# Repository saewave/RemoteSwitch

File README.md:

# RemoteSwitch

Проект RemoteSwitch создан для тех, кто самостоятельно занимается разработкой систем домайшеней автоматизации но сталкивается с рядом проблем, таких как:
- передача данных по радио каналу;
- разработка схемотехники для исполнительных устройств;
- разработка модуля для управления устройствами (хаб);
- организации беспроводной сети.

Проект домашней автоматизации на базе SaeWave RemoteSwitch решает полностью или частично все вышеперечисленные проблемы. На данный момент характеристики системы такие:
- Частота радиоканала 433 МГц.
- Скорость передачи данных от 1200 кБит
- Дальность устойчивого приема на открытом пространстве - 300м (дальность зависит от помех, наличия препятствий и используемых антенн).
- Подтверждение приема - да (при соответствующих настройках)
- Повторение отправки пакета - да (при соответствующих настройках)
- Подпись пакета - CRC
- Возможность обновления прошивки по воздуху

Проект является полностью открытыми, все исходные коды, схемы и списки деталей являются общедоступными для использования и повторения.

Проект распространяется под лицензией GPLv3 - это означает то, что если ваш проект будет полностью или частично построен на базе SaeWave RemoteSwitch он должен быть открытым.

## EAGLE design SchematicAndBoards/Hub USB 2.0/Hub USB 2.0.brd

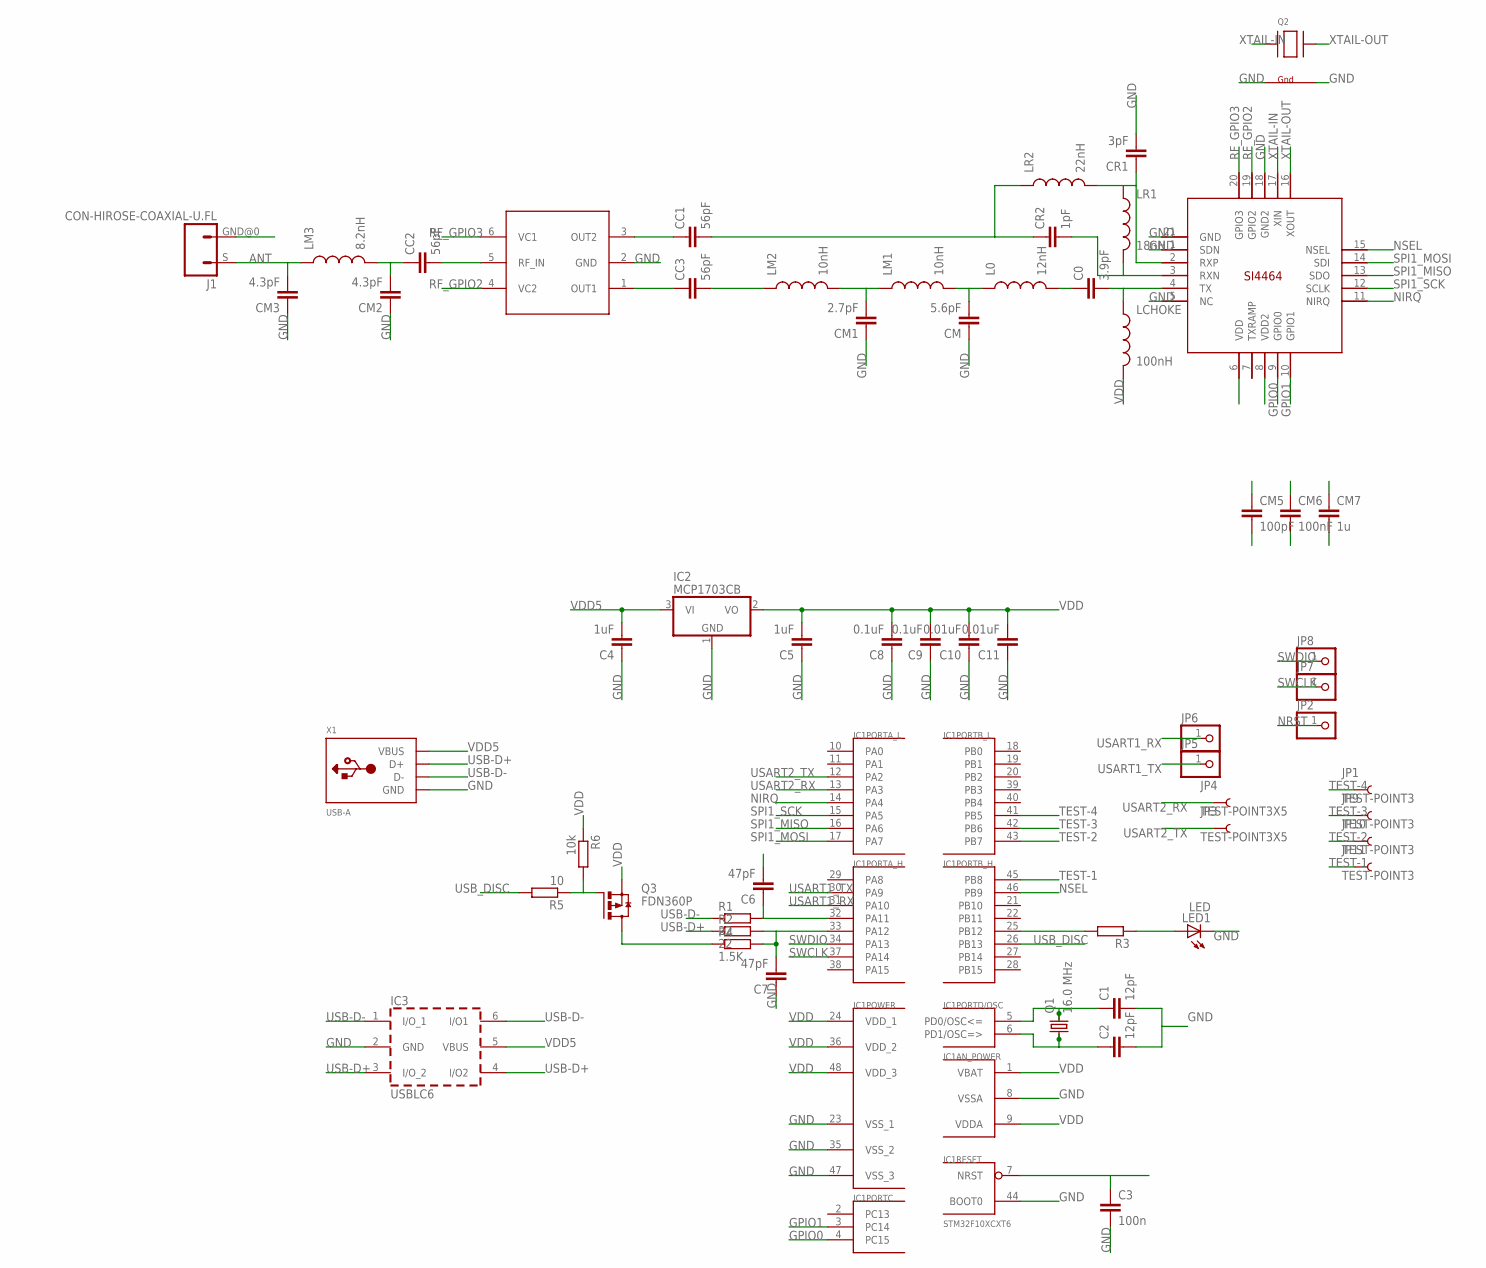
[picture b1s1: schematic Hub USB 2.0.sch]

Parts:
C0: 3.9pF; C0402
C1, C2: 12pF; C0603K
C3: 100n; C0805
C4, C5: 1uF; C0805
C6, C7: 47pF; C0805
C8, C9: 0.1uF; C0805
C10, C11: 0.01uF; C0805
CC1, CC2, CC3: 56pF; C0402
CM: 5.6pF; C0402
CM1: 2.7pF; C0402
CM2, CM3: 4.3pF; C0402
CM5: 100pF; C0402
CM6: 100nF; C0402
CM7: 1u; C0402
CR1: 3pF; C0402
CR2: 1pF; C0402
IC1: STM32F10XCXT6; TQFP48
IC2: MCP1703CB; SOT23
IC3: USBLC6; SOT-23-6L
J1: CON-HIROSE-COAXIAL-U.FL; CON-U.FL
JP1, JP9, JP10, JP11: TEST-POINT3; PAD.03X.03
JP2, JP7, JP8: PINHD-1X1; 1X01
JP3, JP4: TEST-POINT3X5; PAD.03X.05
JP5, JP6: PINHD-1X1CB; 1X01-CLEANBIG
L0: 12nH; C0402
LCHOKE: 100nH; C0402
LED1: LED; CHIPLED_0805
LM1, LM2: 10nH; C0402
LM3: 8.2nH; C0402
LR1: 18nH; C0402
LR2: 22nH; C0402
Q1: 16.0 MHz; CRYSTAL-SMD-3.2X2.5
Q2: XTAL-4-3225; NX3225
Q3: FDN360P; SUPER-SOT3
R1, R2: 22; R0805
R3: R-EU_R0805; R0805
R4: 1.5K; R0805
R5: 10; R0805
R6: 10k; R0805
U$1: SI4464; QFN20+GNDPAD
U$2: UPG2179TB; SUPER_MINIMOLD
X1: USB-A; MOLEX_480371000

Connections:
ANT: CM3.2, J1.S (1), LM3.1
GND: C1.2, C2.2, C3.2, C4.1, C5.1, C6.2, C7.1, C8.1, C9.1, C10.1, C11.1, CM.1, CM1.1, CM2.1, CM3.1, CM5.2, CM6.2, CM7.2, CR1.2, IC1.8 (VSSA), IC1.23 (VSS_1), IC1.35 (VSS_2), IC1.44 (BOOT0), IC1.47 (VSS_3), IC2.1 (GND), IC3.2 (GND), J1.GND@0 (2), LED1.C, Q2.2 (G2), Q2.4 (G1), U$1.1 (SDN), U$1.5 (NC), U$1.18 (GND2), U$1.21 (GND), U$2.2 (GND), X1.4 (GND)
GPIO0: IC1.4 (PC15), U$1.9 (GPIO0)
GPIO1: IC1.3 (PC14), U$1.10 (GPIO1)
unnamed: C1.1, IC1.5 (PD0/OSC<=), Q1.3 (2)
unnamed: C2.1, IC1.6 (PD1/OSC=>), Q1.1
unnamed: C0.2, LCHOKE.1, U$1.4 (TX)
unnamed: LED1.A, R3.1
unnamed: C0.1, L0.2
unnamed: C7.2, IC1.33 (PA12), R2.2, R4.2
unnamed: CM.2, L0.1, LM1.2
unnamed: CM1.2, LM1.1, LM2.2
unnamed: CC2.1, CM2.2, LM3.2
unnamed: C6.1, IC1.32 (PA11), R1.2
unnamed: CC3.1, U$2.1 (OUT1)
unnamed: CR2.2, LR1.2, U$1.3 (RXN)
unnamed: CC1.1, U$2.3 (OUT2)
unnamed: CR1.1, LR1.1, LR2.2, U$1.2 (RXP)
unnamed: IC1.25 (PB12), R3.2
unnamed: CC2.2, U$2.5 (RF_IN)
unnamed: CC3.2, LM2.1
unnamed: CC1.2, CR2.1, LR2.1
unnamed: Q3.3 (D), R4.1
unnamed: Q3.1 (G), R5.1, R6.2
NIRQ: IC1.14 (PA4), U$1.11 (NIRQ)
NRST: C3.1, IC1.7 (NRST), JP2.1
NSEL: IC1.46 (PB9), U$1.15 (NSEL)
RF_GPIO2: U$1.19 (GPIO2), U$2.4 (VC2)
RF_GPIO3: U$1.20 (GPIO3), U$2.6 (VC1)
SPI1_MISO: IC1.16 (PA6), U$1.13 (SDO)
SPI1_MOSI: IC1.17 (PA7), U$1.14 (SDI)
SPI1_SCK: IC1.15 (PA5), U$1.12 (SCLK)
SWCLK: IC1.37 (PA14), JP7.1
SWDIO: IC1.34 (PA13), JP8.1
TEST-1: IC1.45 (PB8), JP11.P$1
TEST-2: IC1.43 (PB7), JP10.P$1
TEST-3: IC1.42 (PB6), JP9.P$1
TEST-4: IC1.41 (PB5), JP1.P$1
USART1_RX: IC1.31 (PA10), JP6.1
USART1_TX: IC1.30 (PA9), JP5.1
USART2_RX: IC1.13 (PA3), JP4.P$1
USART2_TX: IC1.12 (PA2), JP3.P$1
USB-D+: IC3.3 (I/O_2), IC3.4 (I/O2), R2.1, X1.3 (D+)
USB-D-: IC3.1 (I/O_1), IC3.6 (I/O1), R1.1, X1.2 (D-)
USB_DISC: IC1.26 (PB13), R5.2
VDD: C5.2, C8.2, C9.2, C10.2, C11.2, CM5.1, CM6.1, CM7.1, IC1.1 (VBAT), IC1.9 (VDDA), IC1.24 (VDD_1), IC1.36 (VDD_2), IC1.48 (VDD_3), IC2.2 (VO), LCHOKE.2, Q3.2 (S), R6.1, U$1.6 (VDD), U$1.8 (VDD2)
VDD5: C4.2, IC2.3 (VI), IC3.5 (VBUS), X1.1 (VBUS)
XTAIL-IN: Q2.1 (X1), U$1.17 (XIN)
XTAIL-OUT: Q2.3 (X2), U$1.16 (XOUT)

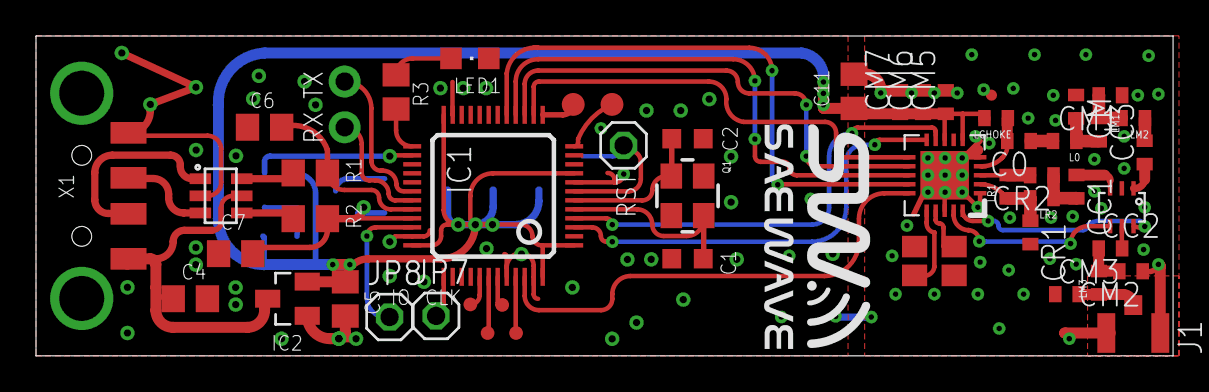
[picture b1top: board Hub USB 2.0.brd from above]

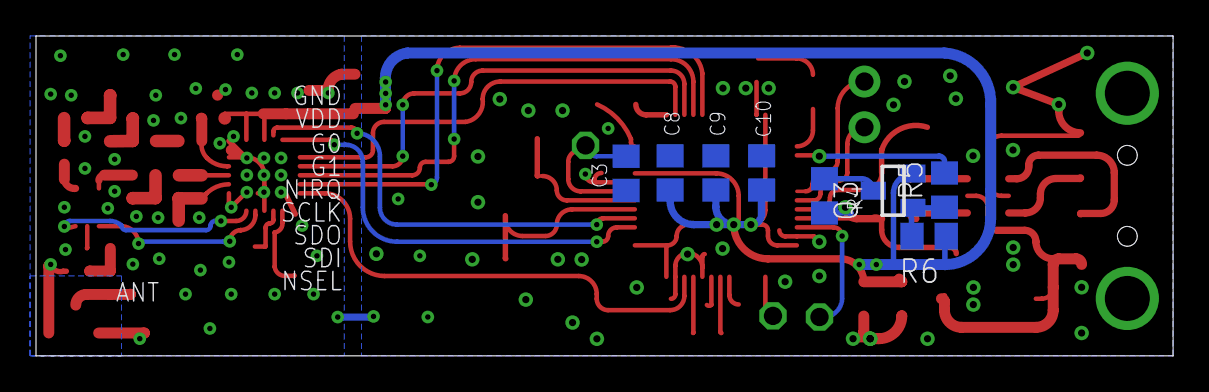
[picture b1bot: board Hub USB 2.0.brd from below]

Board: 2 copper layers, 63.2 x 17.8 mm, 59 parts (8 on the bottom side), 49 nets.

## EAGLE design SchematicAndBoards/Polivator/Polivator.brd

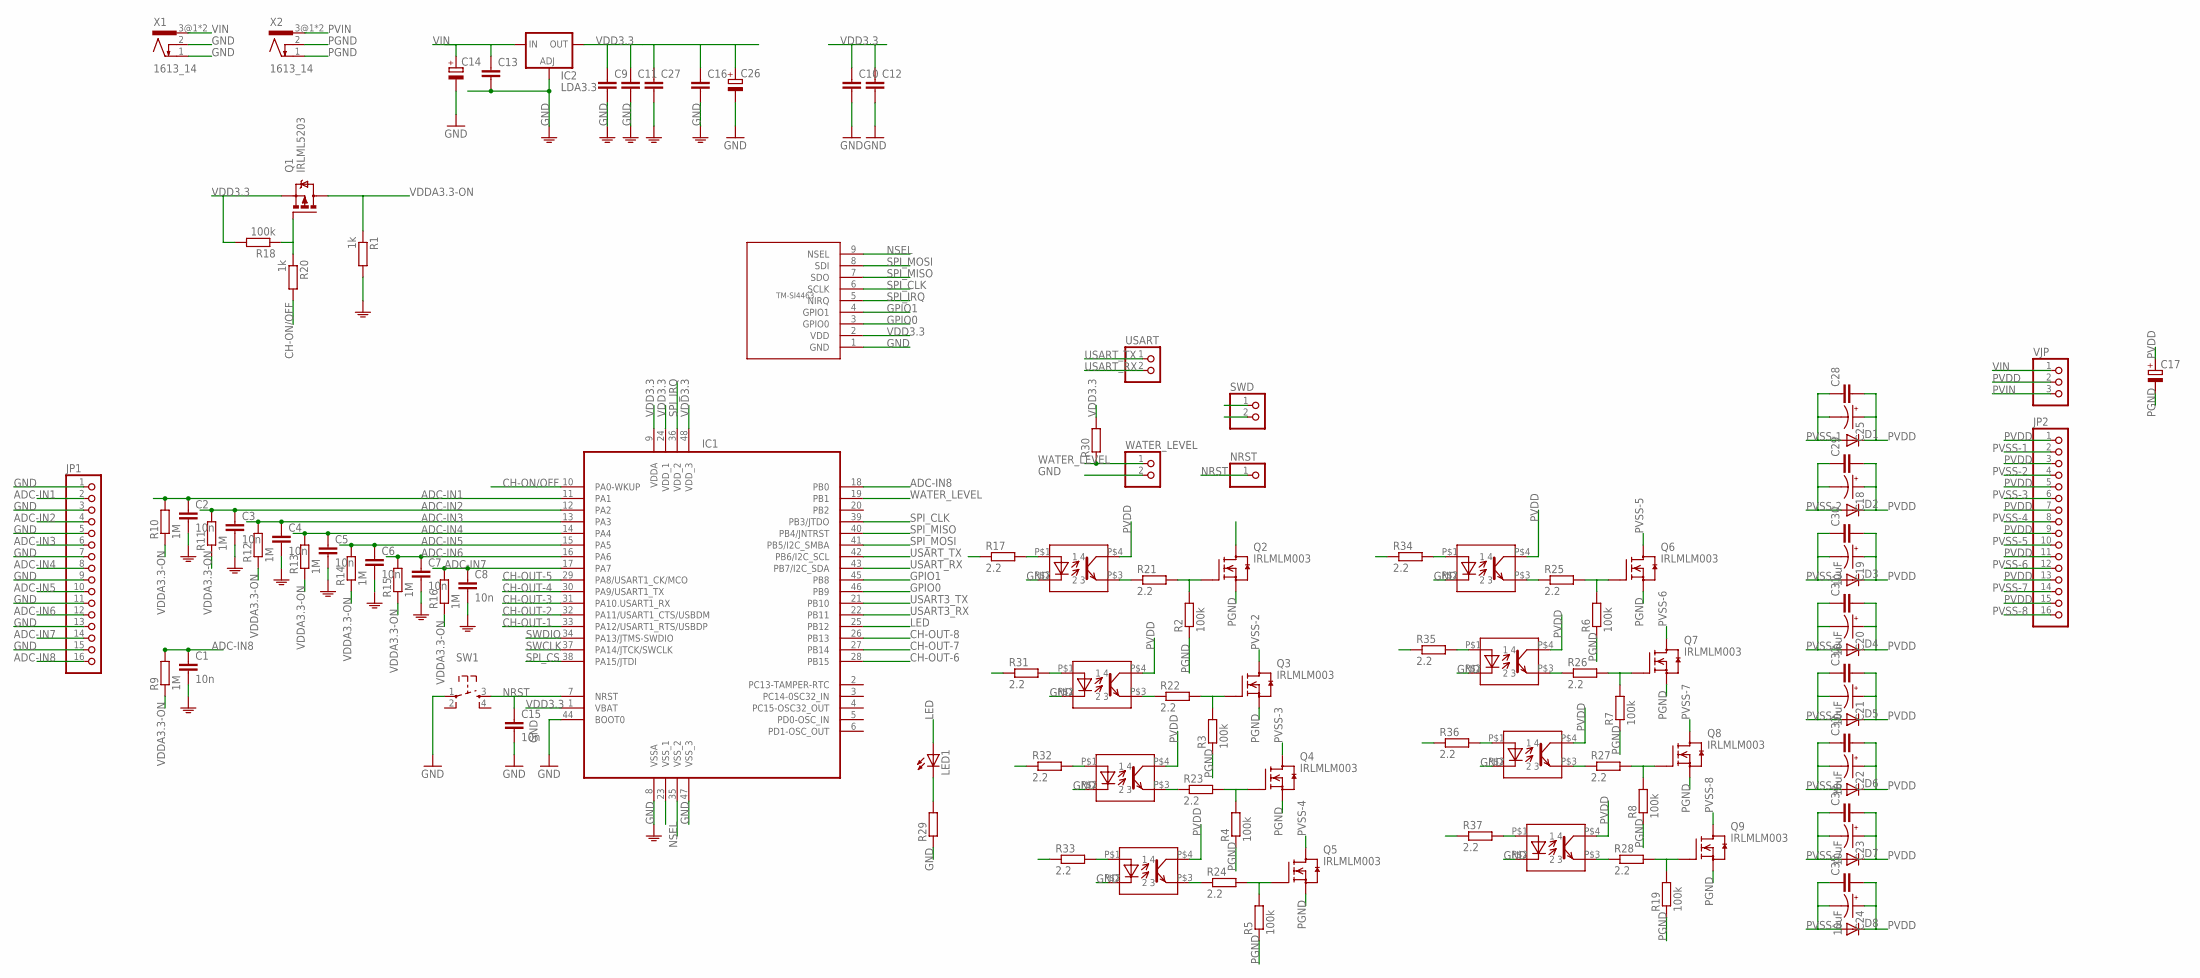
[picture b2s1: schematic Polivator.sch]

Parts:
C1, C2, C3, C4, C5, C6, C7, C8, C15: 10n; C0805
C9, C10: C-EUC3216; C3216
C11, C12, C16, C27, C28, C29, C30, C31, C32, C33, C34, C35: C-EUC0805; C0805
C13: C-EUC1808; C1808
C14, C26: CPOL-EUE2.5-5; E2,5-5
C17: CPOL-EUE2.5-6; E2,5-6
C18, C25: CAP_POL1206; EIA3216
C19, C20, C21, C22, C23, C24: 10uF; EIA3216
D1, D2, D3, D4, D5, D6, D7, D8: DIODE-SOD80C; SOD80C
IC1: IC_UC_STM32; LQFP48
IC2: LDA3.3; SOT223
JP1, JP2: PINHD-1X16; 1X16
LED1: LEDCHIPLED_0805; CHIPLED_0805
NRST: PINHD-1X1; 1X01
Q1: IRLML5203; MICRO3
Q2, Q3, Q4, Q5, Q6, Q7, Q8, Q9: IRLMLM003; SOT23
R1, R20: 1k; R0805
R2, R3, R4, R5, R6, R7, R8, R18, R19: 100k; R0805
R9, R10, R11, R12, R13, R14, R15, R16: 1M; R0805
R17, R21, R22, R23, R24, R25, R26, R27, R28, R31, R32, R33, R34, R35, R36, R37: 2.2; R0805
R29, R30: R-EU_R0805; R0805
SW1: SW_TACT_4P; SW_TACT_SMALL
SWD: PINHD-1X2; 1X02
U$8: TM-SI4463; TM-SI4463-SMD
U$10, U$11, U$13, U$16, U$18, U$20, U$23, U$24: PC817-SMD
USART: PINHD-1X2; 1X02
VJP: PINHD-1X3; 1X03
WATER_LEVEL: PINHD-1X2; 1X02
X1, X2: 1613_14

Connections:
ADC-IN1: C2.1, IC1.11 (PA1), JP1.2, R10.2
ADC-IN2: C3.1, IC1.12 (PA2), JP1.4, R11.2
ADC-IN3: C4.1, IC1.13 (PA3), JP1.6, R12.2
ADC-IN4: C5.1, IC1.14 (PA4), JP1.8, R13.2
ADC-IN5: C6.1, IC1.15 (PA5), JP1.10, R14.2
ADC-IN6: C7.1, IC1.16 (PA6), JP1.12, R15.2
ADC-IN7: C8.1, IC1.17 (PA7), JP1.14, R16.2
ADC-IN8: C1.1, IC1.18 (PB0), JP1.16, R9.2
CH-ON/OFF: IC1.10 (PA0-WKUP), R20.2
CH-OUT-1: IC1.33 (PA12/USART1_RTS/USBDP), R17.1
CH-OUT-2: IC1.32 (PA11/USART1_CTS/USBDM), R31.1
CH-OUT-3: IC1.31 (PA10.USART1_RX), R32.1
CH-OUT-4: IC1.30 (PA9/USART1_TX), R33.1
CH-OUT-5: IC1.29 (PA8/USART1_CK/MCO), R34.1
CH-OUT-6: IC1.28 (PB15), R35.1
CH-OUT-7: IC1.27 (PB14), R36.1
CH-OUT-8: IC1.26 (PB13), R37.1
GND: C1.2, C2.2, C3.2, C4.2, C5.2, C6.2, C7.2, C8.2, C9.2, C10.2, C11.2, C12.2, C13.2, C14.-, C15.2, C16.2, C26.-, C27.2, IC1.8 (VSSA), IC1.23 (VSS_1), IC1.44 (BOOT0), IC1.47 (VSS_3), IC2.1 (ADJ), JP1.1, JP1.3, JP1.5, JP1.7, JP1.9, JP1.11, JP1.13, JP1.15, R1.2, R29.1, SW1.1, U$8.1 (GND), U$10.P$2 (2), U$11.P$2 (2), U$13.P$2 (2), U$16.P$2 (2), U$18.P$2 (2), U$20.P$2 (2), U$23.P$2 (2), U$24.P$2 (2), WATER_LEVEL.2, X1.1, X1.2
GPIO0: IC1.46 (PB9), U$8.3 (GPIO0)
GPIO1: IC1.45 (PB8), U$8.4 (GPIO1)
LED: IC1.25 (PB12), LED1.A
unnamed: LED1.C, R29.2
unnamed: Q2.1 (G), R2.2, R21.2
unnamed: Q3.1 (G), R3.2, R22.2
unnamed: Q1.1 (G), R18.1, R20.1
unnamed: Q4.1 (G), R4.2, R23.2
unnamed: R21.1, U$10.P$3 (3)
unnamed: R22.1, U$11.P$3 (3)
unnamed: Q5.1 (G), R5.2, R24.2
unnamed: Q6.1 (G), R6.2, R25.2
unnamed: Q7.1 (G), R7.2, R26.2
unnamed: Q8.1 (G), R8.2, R27.2
unnamed: Q9.1 (G), R19.2, R28.2
unnamed: R23.1, U$13.P$3 (3)
unnamed: R24.1, U$16.P$3 (3)
unnamed: R25.1, U$18.P$3 (3)
unnamed: R26.1, U$20.P$3 (3)
unnamed: R27.1, U$23.P$3 (3)
unnamed: R28.1, U$24.P$3 (3)
unnamed: R17.2, U$10.P$1 (1)
unnamed: R31.2, U$11.P$1 (1)
unnamed: R32.2, U$13.P$1 (1)
unnamed: R33.2, U$16.P$1 (1)
unnamed: R37.2, U$24.P$1 (1)
unnamed: R36.2, U$23.P$1 (1)
unnamed: R35.2, U$20.P$1 (1)
unnamed: R34.2, U$18.P$1 (1)
NRST: C15.1, IC1.7 (NRST), NRST.1, SW1.3
NSEL: IC1.35 (VSS_2), U$8.9 (NSEL)
PGND: C17.-, Q2.2 (S), Q3.2 (S), Q4.2 (S), Q5.2 (S), Q6.2 (S), Q7.2 (S), Q8.2 (S), Q9.2 (S), R2.1, R3.1, R4.1, R5.1, R6.1, R7.1, R8.1, R19.1, X2.1, X2.2
PVDD: C17.+, C18.A (+), C19.A (+), C20.A (+), C21.A (+), C22.A (+), C23.A (+), C24.A (+), C25.A (+), C28.2, C29.2, C30.2, C31.2, C32.2, C33.2, C34.2, C35.2, D1.C, D2.C, D3.C, D4.C, D5.C, D6.C, D7.C, D8.C, JP2.1, JP2.3, JP2.5, JP2.7, JP2.9, JP2.11, JP2.13, JP2.15, U$10.P$4 (4), U$11.P$4 (4), U$13.P$4 (4), U$16.P$4 (4), U$18.P$4 (4), U$20.P$4 (4), U$23.P$4 (4), U$24.P$4 (4), VJP.2
PVIN: VJP.3, X2.3@1 (3), X2.3@2 (3)
PVSS-1: C25.C (-), C28.1, D1.A, JP2.2, Q2.3 (D)
PVSS-2: C18.C (-), C29.1, D2.A, JP2.4, Q3.3 (D)
PVSS-3: C19.C (-), C30.1, D3.A, JP2.6, Q4.3 (D)
PVSS-4: C20.C (-), C31.1, D4.A, JP2.8, Q5.3 (D)
PVSS-5: C21.C (-), C32.1, D5.A, JP2.10, Q6.3 (D)
PVSS-6: C22.C (-), C33.1, D6.A, JP2.12, Q7.3 (D)
PVSS-7: C23.C (-), C34.1, D7.A, JP2.14, Q8.3 (D)
PVSS-8: C24.C (-), C35.1, D8.A, JP2.16, Q9.3 (D)
SPI_CLK: IC1.39 (PB3/JTDO), U$8.6 (SCLK)
SPI_CS: IC1.38 (PA15/JTDI)
SPI_IRQ: IC1.36 (VDD_2), U$8.5 (NIRQ)
SPI_MISO: IC1.40 (PB4/JNTRST), U$8.7 (SDO)
SPI_MOSI: IC1.41 (PB5/I2C_SMBA), U$8.8 (SDI)
SWCLK: IC1.37 (PA14/JTCK/SWCLK), SWD.2
SWDIO: IC1.34 (PA13/JTMS-SWDIO), SWD.1
USART3_RX: IC1.22 (PB11)
USART3_TX: IC1.21 (PB10)
USART_RX: IC1.43 (PB7/I2C_SDA), USART.2
USART_TX: IC1.42 (PB6/I2C_SCL), USART.1
VDD3.3: C9.1, C10.1, C11.1, C12.1, C16.1, C26.+, C27.1, IC1.1 (VBAT), IC1.9 (VDDA), IC1.24 (VDD_1), IC1.48 (VDD_3), IC2.4 (OUT), Q1.2 (S), R18.2, R30.2, U$8.2 (VDD)
VDDA3.3-ON: Q1.3 (D), R1.1, R9.1, R10.1, R11.1, R12.1, R13.1, R14.1, R15.1, R16.1
VIN: C13.1, C14.+, IC2.3 (IN), VJP.1, X1.3@1 (3), X1.3@2 (3)
WATER_LEVEL: IC1.19 (PB1), R30.1, WATER_LEVEL.1

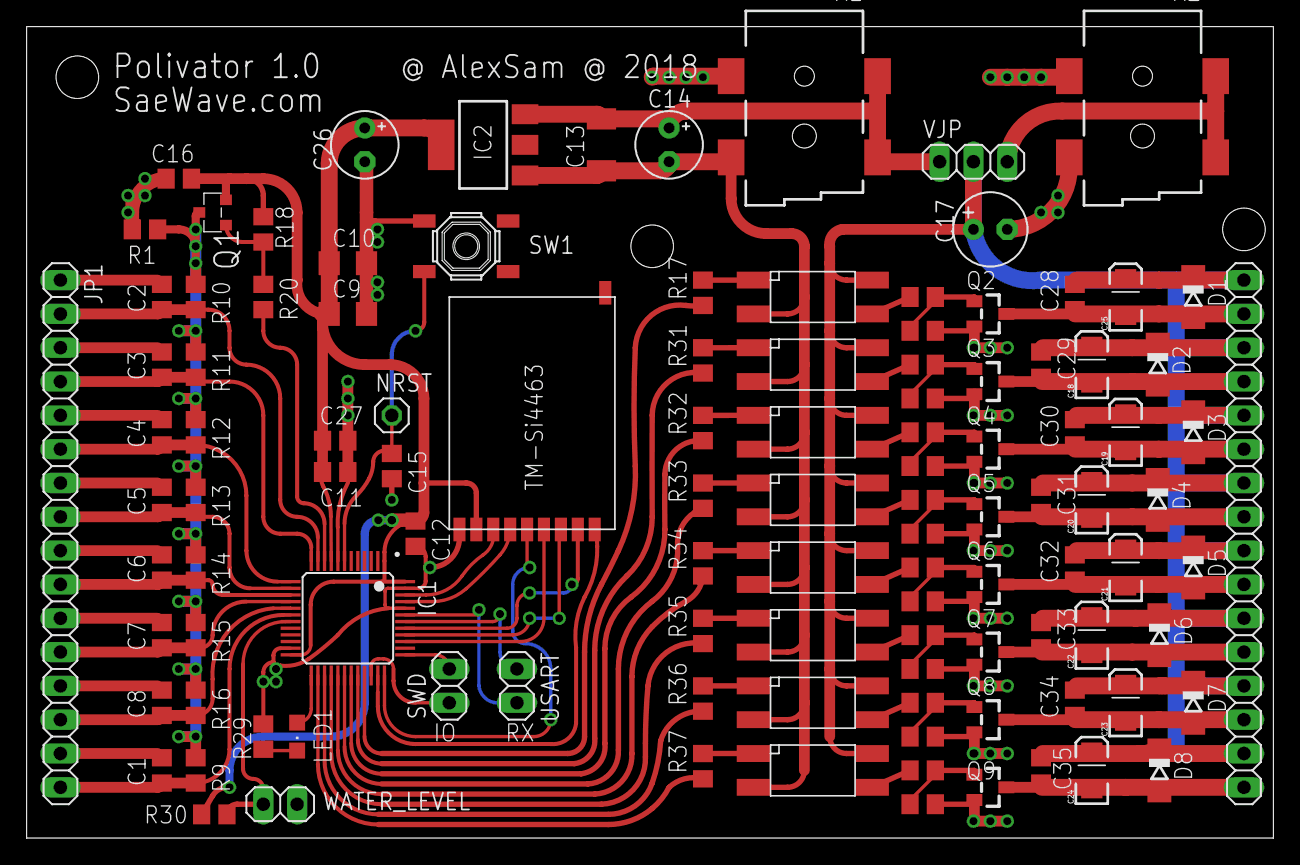
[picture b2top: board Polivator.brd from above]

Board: 2 copper layers, 93.7 x 61.0 mm, 111 parts (0 on the bottom side), 72 nets.

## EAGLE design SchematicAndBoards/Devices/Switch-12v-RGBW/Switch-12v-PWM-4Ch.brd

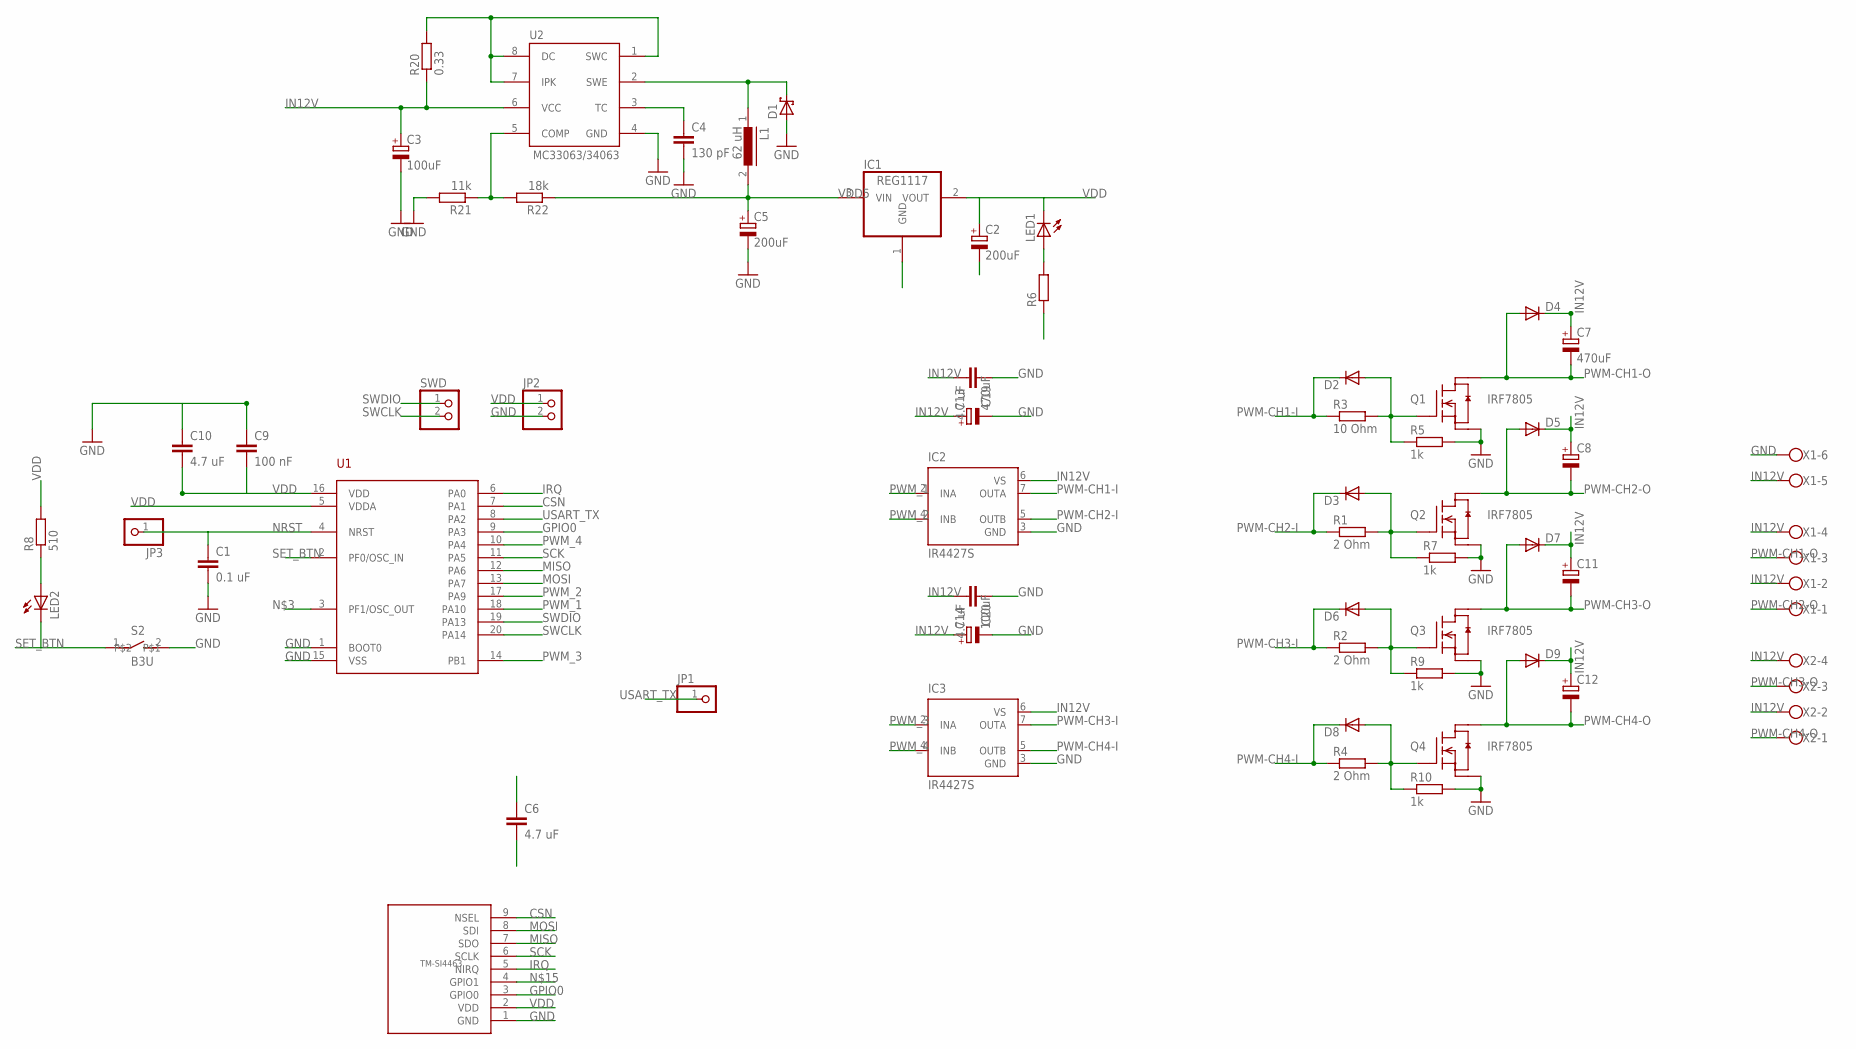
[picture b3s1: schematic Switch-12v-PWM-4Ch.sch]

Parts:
C1: 0.1 uF; C0805
C2, C5: 200uF; SMC_C
C3: 100uF; SMC_C
C4: 130 pF; C0805
C6, C10, C19, C20: 4.7 uF; C0805
C7: 470uF; E5-8,5
C8, C11, C12: CPOL-EUE5-8.5; E5-8,5
C9: 100 nF; C0805
C13: 470uF; 085CS_1AR
C14: 100uF; 085CS_1AR
D1: SCHOTTKY-DIODE; DIODE_SMB
D2, D3, D4, D5, D6, D7, D8, D9: DIODE-DO214BA; DO214BA
IC1: REG1117; SOT223
IC2, IC3: IR4427S; SO08
JP1, JP3: PINHD-1X1; 1X01
JP2: PINHD-1X2; 1X02
L1: 62 uH; DR73
LED1, LED2: LEDCHIPLED_0805; CHIPLED_0805
Q1, Q2, Q3, Q4: IRF7805; SO-8
R1, R2, R4: 2 Ohm; R0805
R3: 10 Ohm; R0805
R5, R7, R9, R10: 1k; R0805
R6: R-EU_R0805; R0805
R8: 510; R0805
R20: 0.33; R0805
R21: 11k; R0805
R22: 18k; R0805
S2: B3U; 1210
SWD: PINHD-1X2; 1X02
U1: STM32F030F4; TSSOP20
U2: MC33063/MC34063D; SO08
U$1: TM-SI4463; TM-SI4463-SMD
X1: W237-6
X2: W237-4

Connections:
CSN: U1.7 (PA1), U$1.9 (NSEL)
GND: C1.2, C2.-, C3.-, C4.2, C5.-, C6.2, C9.1, C10.1, C13.-, C14.-, C19.1, C20.1, D1.A (C), IC1.1 (GND), IC2.3 (GND), IC3.3 (GND), JP2.2, Q1.3 (S), Q2.3 (S), Q3.3 (S), Q4.3 (S), R5.2, R6.1, R7.2, R9.2, R10.2, R21.2, S2.2, U1.1 (BOOT0), U1.15 (VSS), U2.4 (GND), U$1.1 (GND), X1.6
GPIO0: U1.9 (PA3), U$1.3 (GPIO0)
IN12V: C3.+, C7.+, C8.+, C11.+, C12.+, C13.+, C14.+, C19.2, C20.2, D4.C, D5.C, D7.C, D9.C, IC2.6 (VS), IC3.6 (VS), R20.1, U2.6 (VCC), X1.2, X1.4, X1.5, X2.2, X2.4
IRQ: U1.6 (PA0), U$1.5 (NIRQ)
MISO: U1.12 (PA6), U$1.7 (SDO)
MOSI: U1.13 (PA7), U$1.8 (SDI)
unnamed: D2.A, Q1.4 (G), R3.2, R5.1
unnamed: D3.A, Q2.4 (G), R1.2, R7.1
unnamed: LED1.A, R6.2
unnamed: LED2.A, R8.1
unnamed: R21.1, R22.2, U2.5 (COMP)
unnamed: R20.2, U2.1 (SWC), U2.7 (IPK), U2.8 (DC)
unnamed: C4.1, U2.3 (TC)
unnamed: D1.C (A), L1.1, U2.2 (SWE)
unnamed: D6.A, Q3.4 (G), R2.2, R9.1
unnamed: D8.A, Q4.4 (G), R4.2, R10.1
NRST: C1.1, JP3.1, U1.4 (NRST)
PWM-CH1-I: D2.C, IC2.7 (OUTA), R3.1
PWM-CH1-O: C7.-, D4.A, Q1.8 (D), X1.3
PWM-CH2-I: D3.C, IC2.5 (OUTB), R1.1
PWM-CH2-O: C8.-, D5.A, Q2.8 (D), X1.1
PWM-CH3-I: D6.C, IC3.7 (OUTA), R2.1
PWM-CH3-O: C11.-, D7.A, Q3.8 (D), X2.3
PWM-CH4-I: D8.C, IC3.5 (OUTB), R4.1
PWM-CH4-O: C12.-, D9.A, Q4.8 (D), X2.1
PWM_1: IC2.2 (INA), U1.18 (PA10)
PWM_2: IC2.4 (INB), U1.17 (PA9)
PWM_3: IC3.2 (INA), U1.14 (PB1)
PWM_4: IC3.4 (INB), U1.10 (PA4)
SCK: U1.11 (PA5), U$1.6 (SCLK)
SET_BTN: LED2.C, S2.1, U1.2 (PF0/OSC_IN)
SWCLK: SWD.2, U1.20 (PA14)
SWDIO: SWD.1, U1.19 (PA13)
USART_TX: JP1.1, U1.8 (PA2)
VDD: C2.+, C6.1, C9.2, C10.2, IC1.2 (VOUT), JP2.1, LED1.C, R8.2, U1.5 (VDDA), U1.16 (VDD), U$1.2 (VDD)
VDD5: C5.+, IC1.3 (VIN), L1.2, R22.1

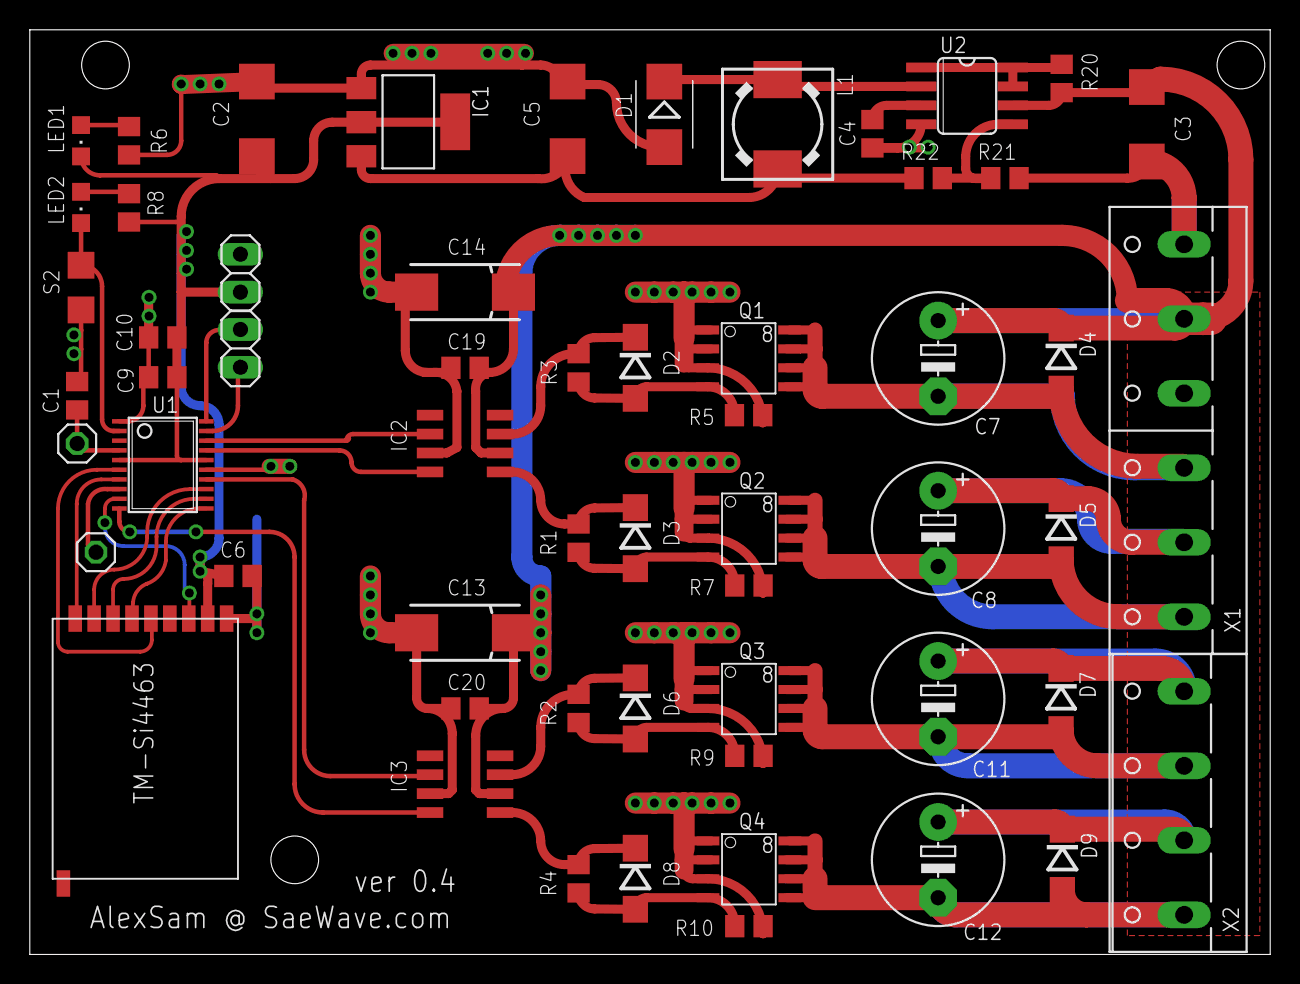
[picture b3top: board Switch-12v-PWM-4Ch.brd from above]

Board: 2 copper layers, 83.2 x 62.1 mm, 58 parts (0 on the bottom side), 37 nets.

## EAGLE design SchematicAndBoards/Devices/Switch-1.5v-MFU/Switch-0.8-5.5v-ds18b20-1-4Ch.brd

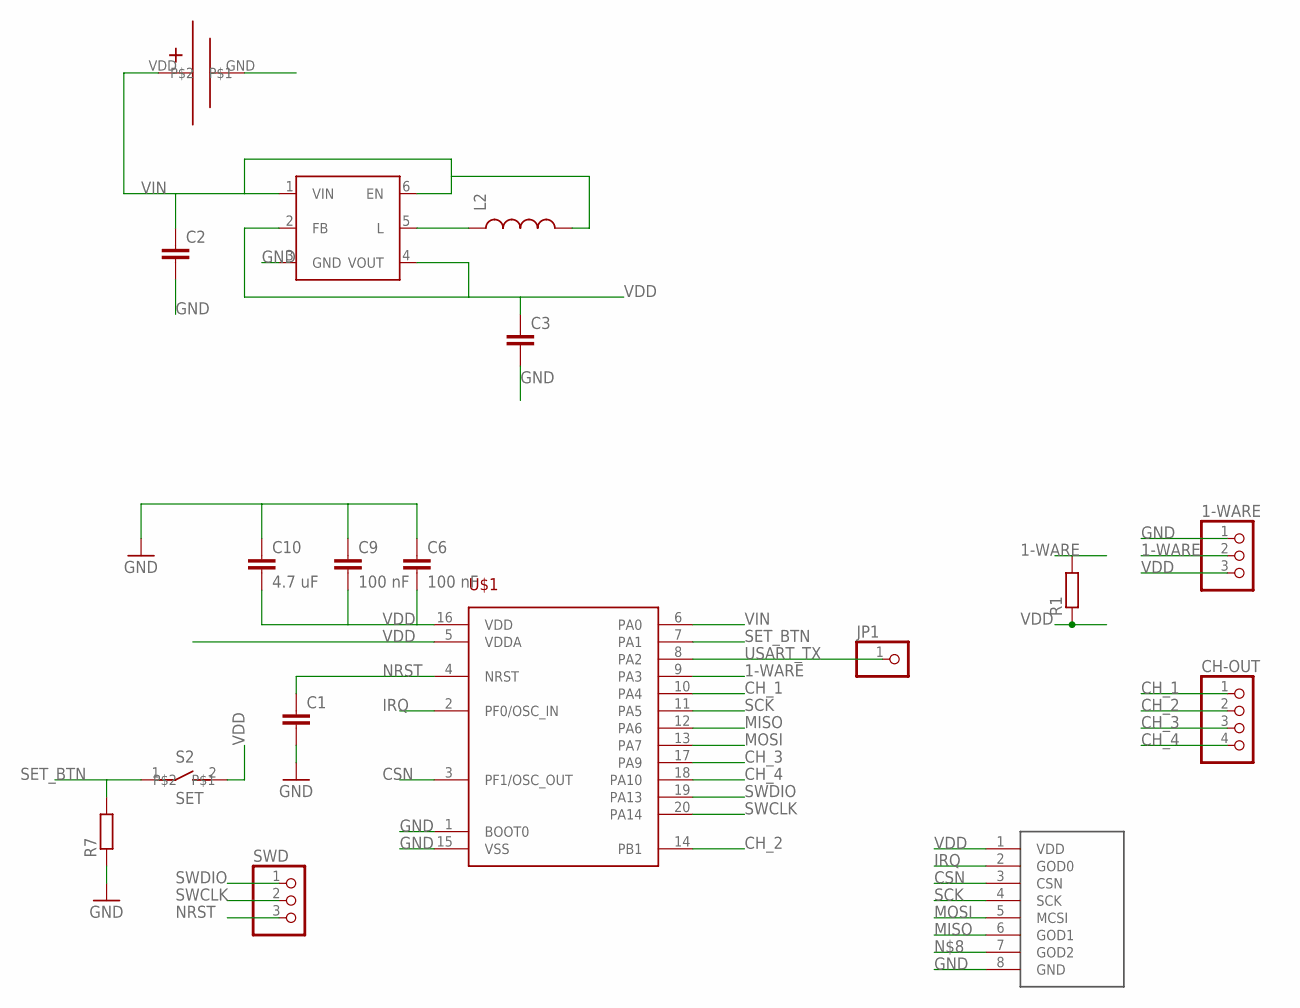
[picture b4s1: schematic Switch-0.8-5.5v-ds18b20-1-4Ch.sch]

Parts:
1-WARE: PINHD-1X3; 1X03
C1, C2, C3: C-EUC0805; C0805
C6, C9: 100 nF; C0805
C10: 4.7 uF; C0805
CH-OUT: PINHD-1X4_2.54; 1X04
JP1: PINHD-1X1CB; 1X01-CLEANBIG
L2: INDUCTOR1210; 1210
R1, R7: R-EU_R0805; R0805
S2: SET; 1210
SWD: PINHD-1X3CB; 1X03-CLEANBIG
U$1: STM32F030F4; TSSOP20
U$2: TPS61221; SC-70-6
U$3: AS07-M1101S
U$4: BAT-AA1-PCB-HOLDER

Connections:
1-WARE: 1-WARE.2, R1.2, U$1.9 (PA3)
CH_1: CH-OUT.1, U$1.10 (PA4)
CH_2: CH-OUT.2, U$1.14 (PB1)
CH_3: CH-OUT.3, U$1.17 (PA9)
CH_4: CH-OUT.4, U$1.18 (PA10)
CSN: U$1.3 (PF1/OSC_OUT), U$3.3 (CSN)
GND: 1-WARE.1, C1.2, C2.2, C3.2, C6.1, C9.1, C10.1, R7.1, U$1.1 (BOOT0), U$1.15 (VSS), U$2.3 (GND), U$3.8 (GND), U$4.GND
IRQ: U$1.2 (PF0/OSC_IN), U$3.2 (GOD0)
MISO: U$1.12 (PA6), U$3.6 (GOD1)
MOSI: U$1.13 (PA7), U$3.5 (MCSI)
unnamed: L2.1, U$2.5 (L)
NRST: C1.1, SWD.3, U$1.4 (NRST)
SCK: U$1.11 (PA5), U$3.4 (SCK)
SET_BTN: R7.2, S2.1, U$1.7 (PA1)
SWCLK: SWD.2, U$1.20 (PA14)
SWDIO: SWD.1, U$1.19 (PA13)
USART_TX: JP1.1, U$1.8 (PA2)
VDD: 1-WARE.3, C3.1, C6.2, C9.2, C10.2, R1.1, S2.2, U$1.5 (VDDA), U$1.16 (VDD), U$2.2 (FB), U$2.4 (VOUT), U$3.1 (VDD)
VIN: C2.1, L2.2, U$1.6 (PA0), U$2.1 (VIN), U$2.6 (EN), U$4.VDD

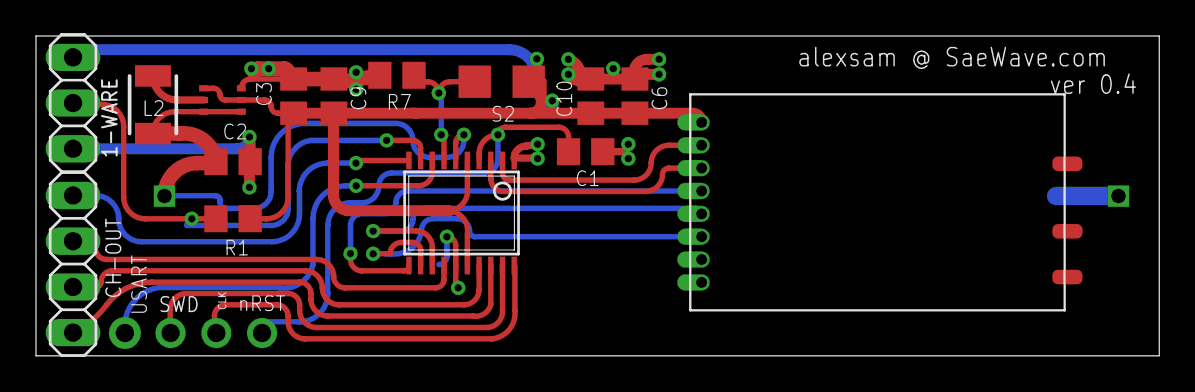
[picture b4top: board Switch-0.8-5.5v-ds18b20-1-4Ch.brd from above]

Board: 2 copper layers, 62.4 x 17.8 mm, 18 parts (1 on the bottom side), 19 nets.

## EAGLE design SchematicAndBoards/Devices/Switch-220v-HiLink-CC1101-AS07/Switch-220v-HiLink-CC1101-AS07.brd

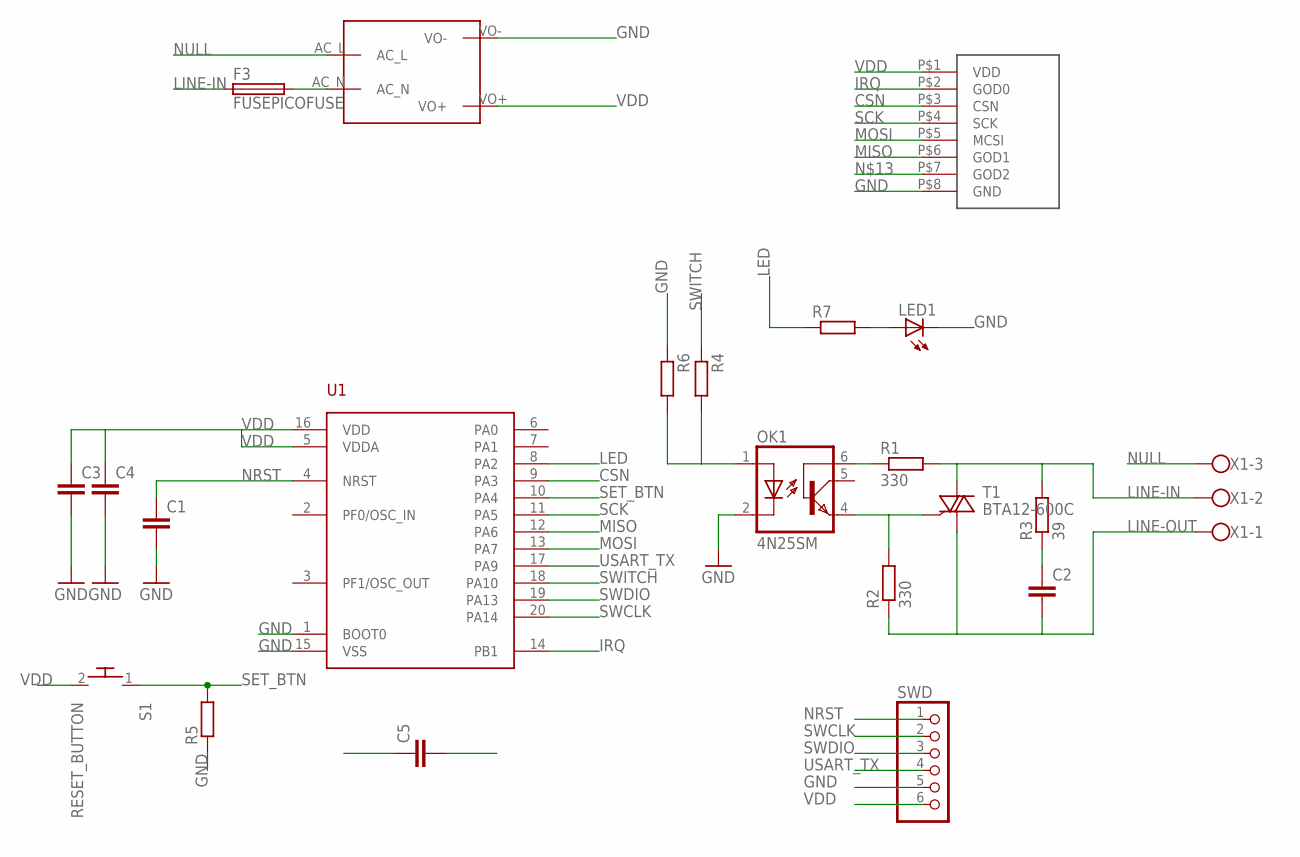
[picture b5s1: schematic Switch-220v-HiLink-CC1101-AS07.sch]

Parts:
C1, C3, C4, C5: C-EUC0805; C0805
C2: C-EU050-025X075; C050-025X075
F3: FUSEPICOFUSE; PICOFUSE
LED1: LEDCHIP-LED0805; CHIP-LED0805
OK1: 4N25SM; DIL6-SMD
R1: 330; 0207/2V
R2: 330; 0204/7
R3: 39; 0204/7
R4, R5, R6, R7: R-EU_R0805; R0805
S1: RESET_BUTTON; EVQ-PJU05K
SWD: PINHD-1X6B; 1X06-BIG
T1: BTA12-600C; TO220DS
U1: STM32F030F4; TSSOP20
U$2: MAINS_CONVERTERS; HLK-PM01
U$4: AS07-M1101SSMD; AS07-M1101S-SMD
X1: W237-103

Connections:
CSN: U1.9 (PA3), U$4.P$3 (CSN)
GND: C1.2, C3.2, C4.2, C5.1, LED1.C, OK1.2 (C), R5.1, R6.1, SWD.5, U1.1 (BOOT0), U1.15 (VSS), U$2.VO-, U$4.P$8 (GND)
IRQ: U1.14 (PB1), U$4.P$2 (GOD0)
LED: R7.1, U1.8 (PA2)
LINE-IN: F3.1, R1.2, R3.2, T1.A2, X1.2
LINE-OUT: C2.2, R2.1, T1.A1, X1.1
MISO: U1.12 (PA6), U$4.P$6 (GOD1)
MOSI: U1.13 (PA7), U$4.P$5 (MCSI)
unnamed: OK1.4 (EMI), R2.2, T1.G
unnamed: OK1.6 (BAS), R1.1
unnamed: LED1.A, R7.2
unnamed: F3.2, U$2.AC_N
unnamed: C2.1, R3.1
unnamed: OK1.1 (A), R4.2, R6.2
NRST: C1.1, SWD.1, U1.4 (NRST)
NULL: U$2.AC_L, X1.3
SCK: U1.11 (PA5), U$4.P$4 (SCK)
SET_BTN: R5.2, S1.1, U1.10 (PA4)
SWCLK: SWD.2, U1.20 (PA14)
SWDIO: SWD.3, U1.19 (PA13)
SWITCH: R4.1, U1.18 (PA10)
USART_TX: SWD.4, U1.17 (PA9)
VDD: C3.1, C4.1, C5.2, S1.2, SWD.6, U1.5 (VDDA), U1.16 (VDD), U$2.VO+, U$4.P$1 (VDD)

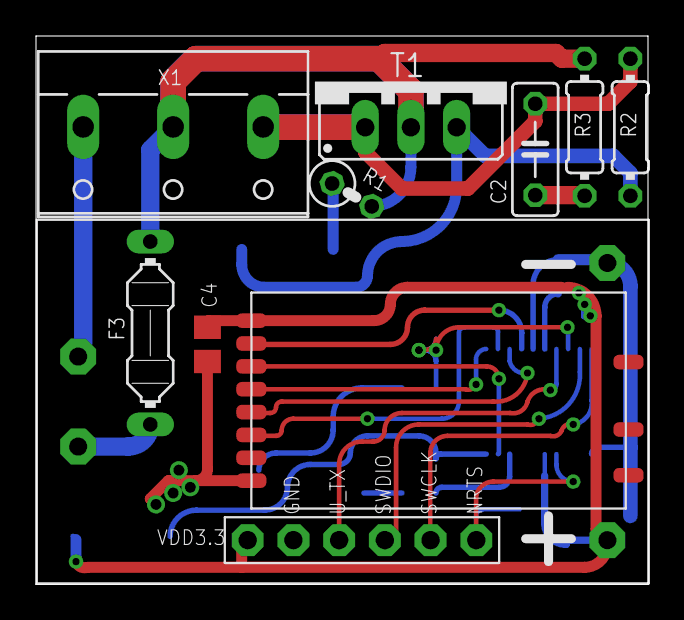
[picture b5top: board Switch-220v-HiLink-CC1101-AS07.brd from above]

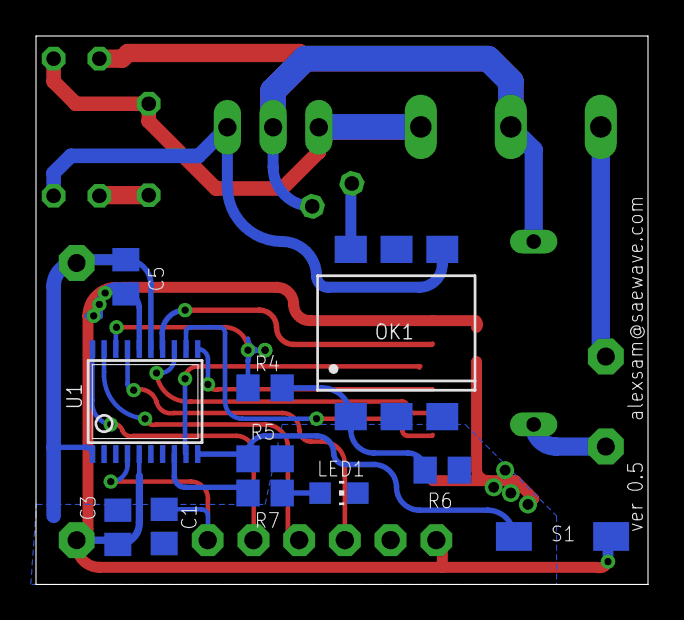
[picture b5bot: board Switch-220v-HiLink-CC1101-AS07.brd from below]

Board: 2 copper layers, 34.0 x 30.5 mm, 22 parts (11 on the bottom side), 23 nets.

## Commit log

2016-04-08 Temporary commit
2016-04-22 Remove format depending type
2016-04-22 Add Switch-220v-8Ch
2016-04-22 Change config in Nucleo401RE_RTOS
2016-05-18 New Lib
2016-05-18 New Switch-1Ware-4Ch-p
2016-05-18 Change reference to arrays
2016-05-20 Fix some errors in Device when send package to Hub
2016-08-18 Beautify code and add some comments
2016-08-19 Remove unnecessary file
2016-08-19 Rename Lib to DeviceLib-F030
2016-08-19 Small text correction
2016-12-13 Code refactor and new template for STM32F030F4
2016-12-13 Code Refactor
2016-12-16 Add Bootloader template Switch-Template, some refactoring
2016-12-16 Remove debug from main loop
2016-12-16 Use low power template for 1Wire thermometer
2016-12-16 Fix bug in RTC Alarm config
2017-01-17 Add RPi HUB STM32F103
2017-01-17 Add __NOP
2017-01-17 Add PowerOff to save power consumption
2017-01-17 Fix wrong pin
2017-01-17 Add PowerOff to DeviceLib
2017-01-17 Update .clang-format
2017-01-17 Add files for HUB STM32F103
2017-01-17 Update old 401RE Hub
2017-05-05 Add Eagle Schematic and Boards for USB Hub, 220 AC switch and AA bat remote device
2017-05-05 Eagle library for Devices and Hub
2017-05-11 Add 4Ch 12V controller
2017-05-11 Update Switch-12v-PWM-4Ch
2017-05-11 Update Switch-12v-PWM-4Ch - replace driver to IR4427S
2017-05-27 Add new device Switch-1Ware-4Ch-CC1101-F030F4
2017-05-27 Add Eagle boad and schematic for device Switch-1Ware-4Ch-CC1101-F030F4
2017-08-20 Update schematic and boards
2017-10-16 Add libraries
2017-12-10 Add FWUpdater
2017-12-17 Add Switch-Template-CC1101-F030
2017-12-17 Remove Switch-1Ware-4Ch-CC1101-F030F4
2017-12-17 Remove Switch-Template, Switch-1Ware-4Ch-p, 'Switch-1Ware-4Ch as legacy code
2017-12-17 Add Switch-4Ch-CC1101-F030F4 as main device for new board
2017-12-17 Add Keil project files
2017-12-17 Remove legacy code
2017-12-17 Update FWUpdater and add code for emulate devices
2017-12-24 Add Hub-F103-USB-Stick-CC1101
2017-12-24 Update Switch-4Ch-CC1101-F030F4
2018-02-18 Fix minor bugs in Hub-F103-USB-Stick-CC1101
2018-02-18 Change output power to 10dB for transmitter
2018-02-19 Change TIM_Configure
2018-02-19 Disable TIM_Configure()
2018-02-19 Create LICENSE
2018-05-27 Add CRC32 checksum
2018-05-27 Update Hub USB 2.0 schematic
2018-05-27 Update Switch-12v-PWM-4Ch schematic
2018-05-27 Add Bootloader for STM32F103 to update firmware
2018-05-27 Butify main.c
2018-07-11 Release Polivator
2018-07-11 Butify Polivator
2018-07-11 Add Polivator to SchematicAndBoards
2018-08-24 Update Hub USB 2.0, add achematic in PDF
2018-08-24 Add Hub USB 2.0 Bot.png & Hub USB 2.0 Top.png
2018-08-24 Add Hub USB 2.0 Bottom.png

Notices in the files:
parts and their libraries:
SparkFun-Passives: Licensing: Creative Commons ShareAlike 4.0 International - https://creativecommons.org/licenses/by-sa/4.0
m-pad-2.1: License : GNU General Public License version 2 (see bottom)
